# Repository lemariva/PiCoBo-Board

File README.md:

# PiCoBo-Board 

**PiCoBo** is a multi-target board. I designed it using the **MSP430G2553** (20/28 pin version), which is part of the MSP430 Texas Instruments family of ultra-low-power microcontrollers. 

The board includes also a **CP2102** which can be used for communication over UART. 

The board can be supplied using a C2032 battery, over USB or external DC source up to 10V. It uses a **TPS77301DGK** to regulate the max. voltage of 3.6V needed for the MSP430. 

Up to three **IRLL2705** can be soldered to the board to switch on/off directly (or using PWM) voltages up to 55V and 3.8A. Additionall multiple pinouts are available to connect external sensors (e.g. **DHT11**), servo motors, leds etc. For testing uses it can be programmed using the MSP430G2553 LaunchPad.

Applications
-------------------
* Ultra-low-power sensor: 
	* Temperature
	* Humidity
	* Air quality
	* Light condition
	* Door or window open/close status
	* etc
* Servo controller
* RGB LED controller
* X actuator
* etc

PCB Boards
-----

More Info: 
-------------------

* Blog article related to this project: https://goo.gl/yuvsjp
* Code example: https://goo.gl/CPGcYK
* Datasheet MSP430G2553: http://www.ti.com/product/MSP430G2553

Changelog
-------------------
* Revision: 1.1v

License
--------------------
Apache 2.0

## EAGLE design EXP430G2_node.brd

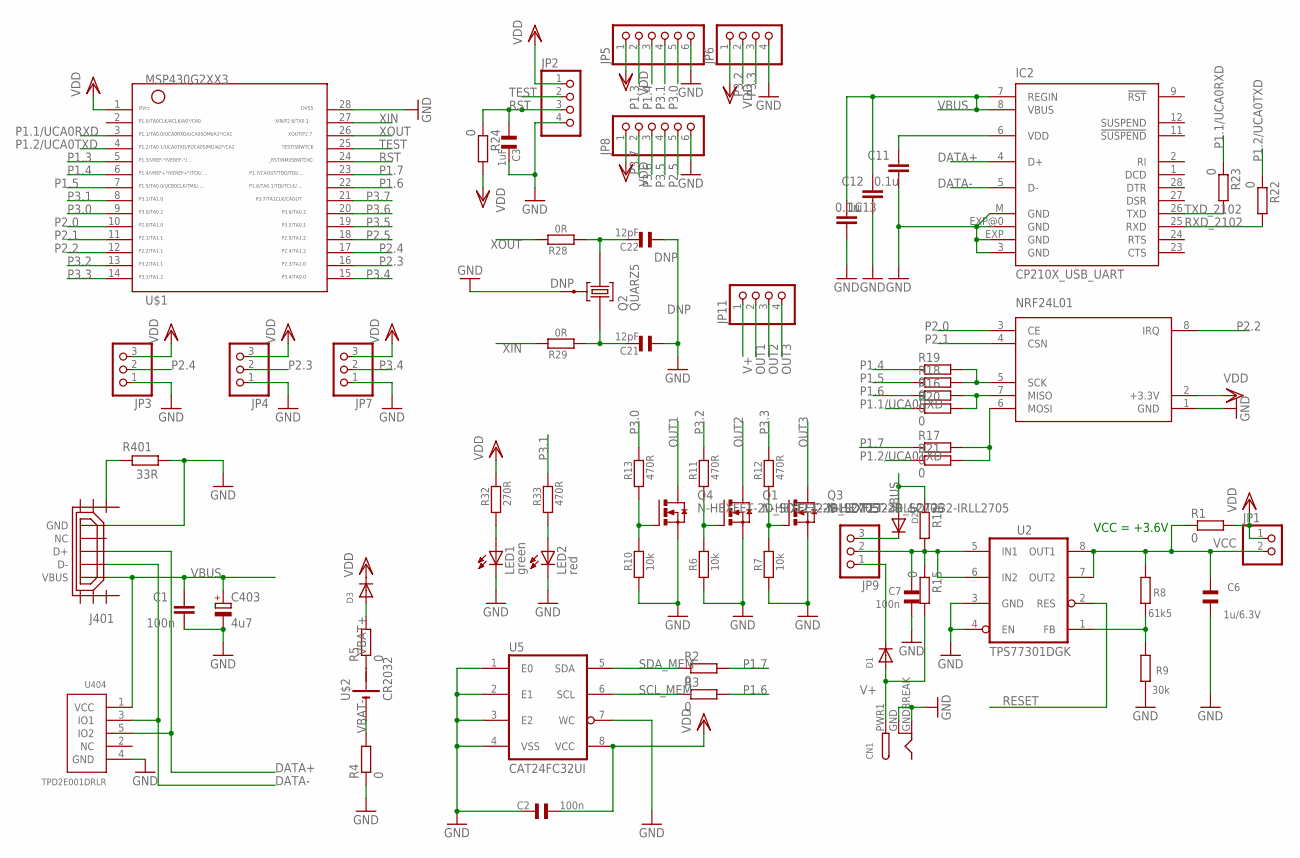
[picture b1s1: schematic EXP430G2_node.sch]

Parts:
C1: 100n; C0603
C2, C7: 100n; 0603
C3: 1uF; 0603
C6: 1u/6.3V; 0603
C11, C13: 0.1u; C0603
C12: 1u; C0603
C21, C22: 12pF; 0603
C403: 4u7; A/3216-18R
CN1: DCBARRELSMT; DCJACK_2MM_SMT
D1, D2, D3: DIODESOT23_REFLOW; SOT23-R
IC2: CP210X_USB_UART; MLP28
J401: USB_MICRO_FLIPPED; HIROSE-ZX62R-B-5P
JP1: PINHD-1X2; 1X02
JP2: PINHD-1X4; 1X04
JP3, JP7, JP9: PINHD-1X3; 1X03
JP4: PINHD-1X3_2.00; 1X03M
JP5, JP8: PINHD-1X6_2.00; 1X06M
JP6, JP11: PINHD-1X4_2.00; 1X04M
LED1: green; DIODE0603
LED2: red; DIODE0603
NRF24L01: NRF24L01HP; NRF24L01_HP
Q1, Q3, Q4: N-HEXFET-2D_SOT232-IRLL2705; SOT223
Q2: QUARZ5
R1, R2, R3, R4, R5, R14, R15, R16, R17, R18, R19, R20, R21, R22, R23, R24: 0; R0201
R6, R7, R10: 10k; 0603
R8: 61k5; 0603
R9: 30k; 0603
R11, R12, R13, R33: 470R; 0603
R28, R29: 0R; 0603
R32: 270R; 0603
R401: 33R; R0603
U2: TPS77301DGK; MSOP8
U5: CAT24FC32UI; TSSOP8
U404: TPD2E001DRLR; TPD2E001-DRL
U$1: G2XX3---PW28; PW28
U$2: CR2032

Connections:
DATA+: IC2.4 (D+), J401.D+, U404.5 (IO2)
DATA-: IC2.5 (D-), J401.D-, U404.3 (IO1)
GND: C1.2, C2.2, C3.2, C6.2, C7.1, C11.2, C12.2, C13.2, C21.1, C22.1, C403.-, CN1.GND (GNDBREAK), CN1.GNDBREAK (GND), IC2.3 (GND), IC2.EXP (GND), IC2.EXP@0 (GND), IC2.M (GND), J401.GND, JP2.4, JP3.1, JP4.1, JP5.6, JP6.4, JP7.1, JP8.6, LED1.K (C), LED2.K (C), NRF24L01.1 (GND), Q1.3 (S), Q2.GND@0 (0), Q3.3 (S), Q4.3 (S), R4.1, R6.1, R7.1, R9.1, R10.1, R401.2, U2.3 (GND), U2.4 (EN), U5.1 (E0), U5.2 (E1), U5.3 (E2), U5.4 (VSS), U5.7 (WC), U404.4 (GND), U$1.28
unnamed: C7.2, JP9.2, R14.2, R15.1, U2.5 (IN1), U2.6 (IN2)
unnamed: D1.3 (C), JP9.1
unnamed: R8.1, R9.2, U2.1 (FB)
unnamed: D3.1 (A), R5.2
unnamed: Q1.1 (G), R6.2, R11.1
unnamed: NRF24L01.7 (MISO), R16.2, R20.2
unnamed: Q3.1 (G), R7.2, R12.1
unnamed: NRF24L01.6 (MOSI), R17.2, R21.2
unnamed: J401.SHIELD1, R401.1
unnamed: Q4.1 (G), R10.2, R13.1
unnamed: NRF24L01.5 (SCK), R18.2, R19.2
unnamed: LED2.A, R33.1
unnamed: C11.1, IC2.6 (VDD)
unnamed: LED1.A, R32.1
OUT1: JP11.2, Q4.2 (D), Q4.4 (D)
OUT2: JP11.3, Q1.2 (D), Q1.4 (D)
OUT3: JP11.4, Q3.2 (D), Q3.4 (D)
P1.1/UCA0RXD: R20.1, R23.1, U$1.3
P1.2/UCA0TXD: R21.1, R22.1, U$1.4
P1.3: JP5.2, U$1.5
P1.4: JP5.3, R19.1, U$1.6
P1.5: R18.1, U$1.7
P1.6: R3.2, R16.1, U$1.22
P1.7: R2.2, R17.1, U$1.23
P2.0: NRF24L01.3 (CE), U$1.10
P2.1: NRF24L01.4 (CSN), U$1.11
P2.2: NRF24L01.8 (IRQ), U$1.12
P2.3: JP4.2, U$1.16
P2.4: JP3.2, U$1.17
P2.5: JP8.5, U$1.18
P3.0: JP5.5, R13.2, U$1.9
P3.1: JP5.4, R33.2, U$1.8
P3.2: JP6.2, R11.2, U$1.13
P3.3: JP6.3, R12.2, U$1.14
P3.4: JP7.2, U$1.15
P3.5: JP8.4, U$1.19
P3.6: JP8.3, U$1.20
P3.7: JP8.2, U$1.21
RESET: U2.2 (RES)
RST: C3.1, JP2.3, R24.1, U$1.24
RXD_2102: IC2.25 (RXD), R22.2
SCL_MEM: R3.1, U5.6 (SCL)
SDA_MEM: R2.1, U5.5 (SDA)
TEST: JP2.2, U$1.25
TXD_2102: IC2.26 (TXD), R23.2
V+: CN1.PWR1 (PWR), D1.1 (A), JP11.1, R15.2
VBAT+: R5.1, U$2.P$1 (+)
VBAT-: R4.2, U$2.P$2 (-)
VBUS: C1.1, C12.1, C13.1, C403.+, D2.1 (A), IC2.7 (REGIN), IC2.8 (VBUS), J401.VBUS, R14.1, U404.1 (VCC)
VBUS+: D2.3 (C), JP9.3
VCC: C6.1, JP1.2, R1.1, R8.2, U2.7 (OUT2), U2.8 (OUT1)
VDD: C2.1, D3.3 (C), JP1.1, JP2.1, JP3.3, JP4.3, JP5.1, JP6.1, JP7.3, JP8.1, NRF24L01.2 (+3.3V), R1.2, R24.2, R32.2, U5.8 (VCC), U$1.1
XIN: R29.2, U$1.27
XINR: C21.2, Q2.2, R29.1
XOUT: R28.2, U$1.26
XOUTR: C22.2, Q2.1, R28.1

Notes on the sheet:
VCC = +3.6V
DNP

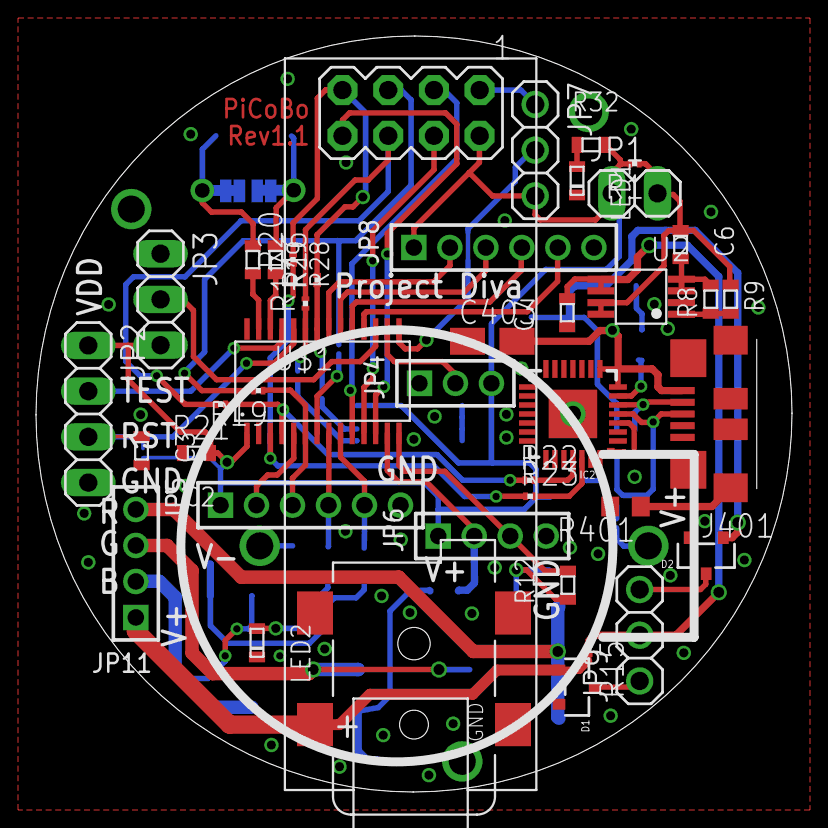
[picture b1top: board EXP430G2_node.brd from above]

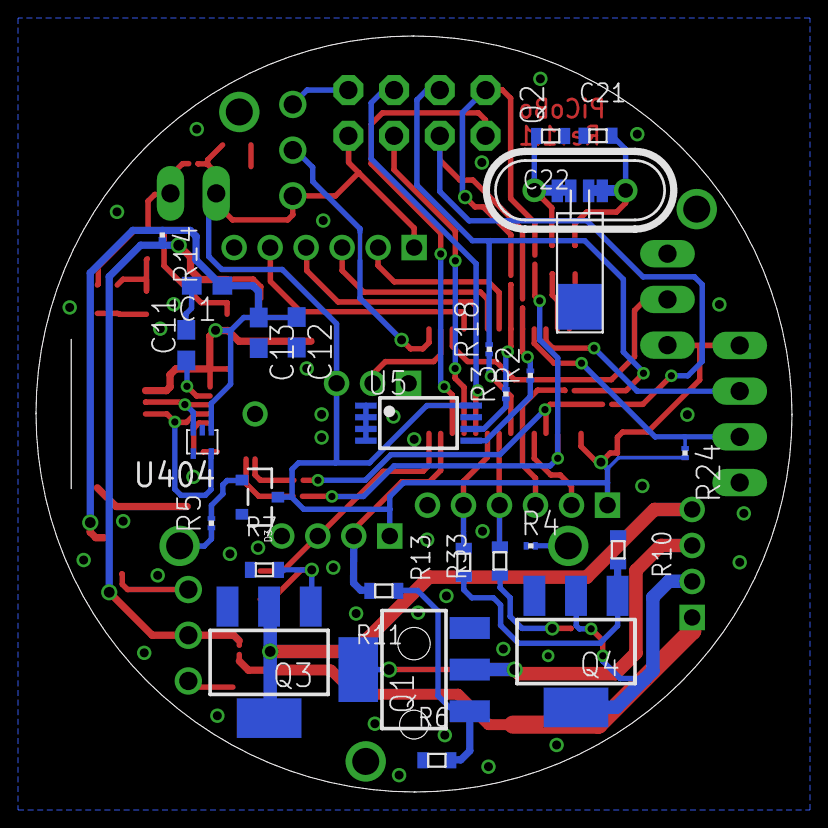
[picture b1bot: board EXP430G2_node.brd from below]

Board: 2 copper layers, 42.0 x 42.0 mm, 68 parts (26 on the bottom side), 58 nets.

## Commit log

2017-07-01 link correction
2017-07-01 added exp430g2 nodes - rev1.1
2017-07-01 changed revision and file name
2017-10-17 readme changes and license file added
